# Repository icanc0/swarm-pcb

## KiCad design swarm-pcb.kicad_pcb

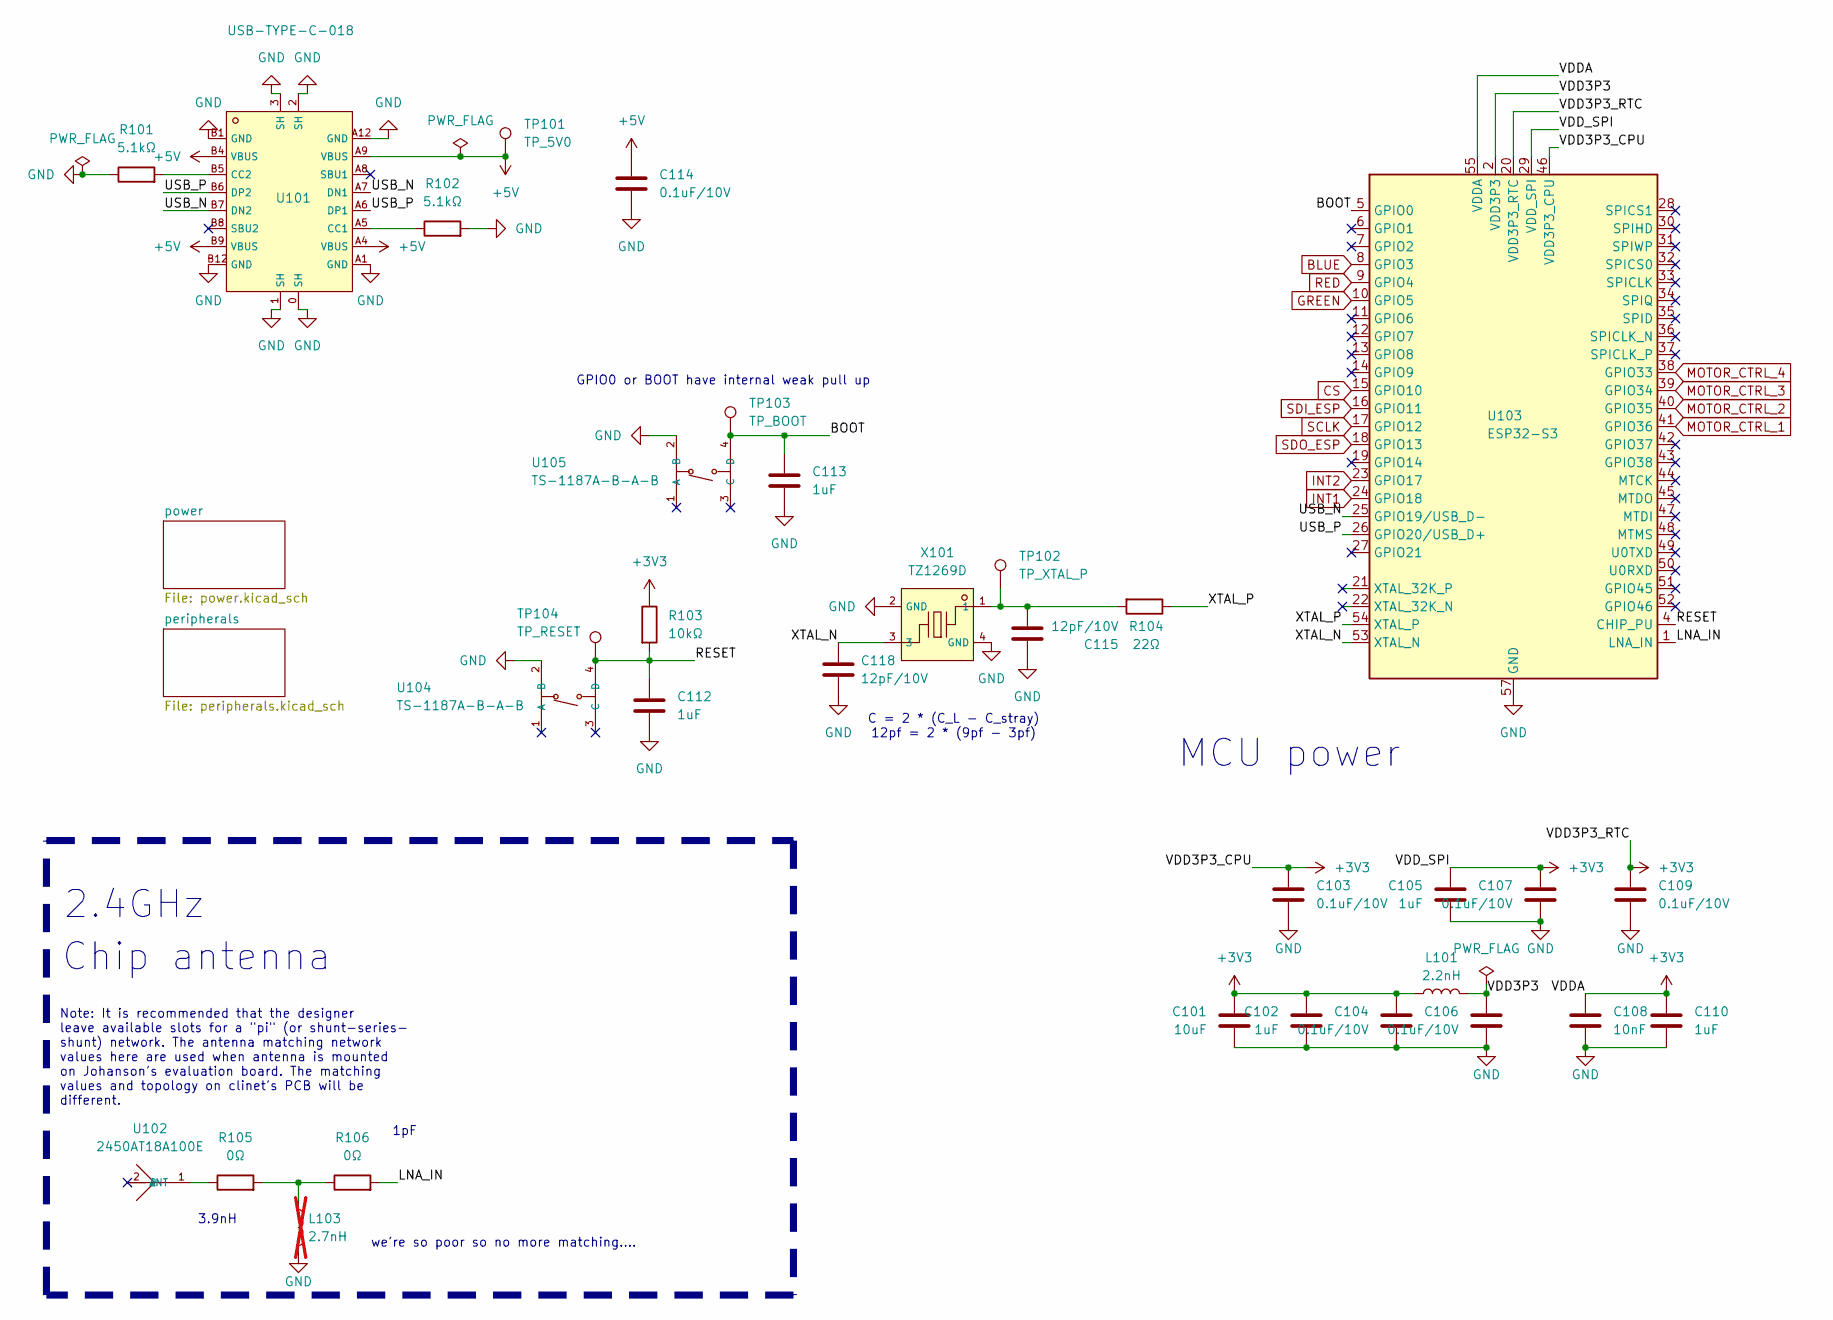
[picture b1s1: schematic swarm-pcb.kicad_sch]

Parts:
C101: 10uF; C_0603_1608Metric
C102, C105, C110, C112, C113: 1uF; C_0603_1608Metric
C103, C104, C106, C107, C109, C114: 0.1uF/10V; C_0402_1005Metric
C108: 10nF; C_0402_1005Metric
C115, C118: 12pF/10V; C_0603_1608Metric
L101: 2.2nH; L_0402_1005Metric
L103: 2.7nH; L_0402_1005Metric; not fitted
R101, R102: 5.1kΩ; R_0402_1005Metric
R103: 10kΩ; L_0402_1005Metric
R104: 22Ω; R_0402_1005Metric
R105, R106: 0Ω; R_0402_1005Metric
TP101: TP_5V0; Pin_D1.0mm_L10.0mm
TP102: TP_XTAL_P; Pin_D1.0mm_L10.0mm
TP103: TP_BOOT; Pin_D1.0mm_L10.0mm
TP104: TP_RESET; Pin_D1.0mm_L10.0mm
U101: USB-TYPE-C-018; USB-C_SMD-TYPE-C-31-M-12; LCSC C2927038
U102: 2450AT18A100E; ANT-SMD_L3.2-W1.6; LCSC C89334
U103: ESP32-S3; QFN-56-1EP_7x7mm_P0.4mm_EP4x4mm
U104, U105: TS-1187A-B-A-B; SW-SMD_4P-L5.1-W5.1-P3.70-LS6.5-TL-2; LCSC C318884
X101: TZ1269D; CRYSTAL-SMD_4P-L2.0-W1.6-BL-A; LCSC C501798

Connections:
+3V3: C101.1, C102.1, C103.1, C104.1, C105.1, C107.1, C108.1, C109.1, C110.1, L101.2, R103.1, U103.20 (VDD3P3_RTC), U103.29 (VDD_SPI), U103.46 (VDD3P3_CPU), U103.55 (VDDA), U103.56 (VDDA); also elsewhere on the board
+5V: C114.1, TP101.1, U101.A4 (VBUS), U101.A9 (VBUS), U101.B4 (VBUS), U101.B9 (VBUS); also elsewhere on the board
/BOOT: C113.1, TP103.1, U103.5 (GPIO0), U105.4 (D)
/LNA_IN: R106.2, U103.1 (LNA_IN)
/RESET: C112.1, R103.2, TP104.1, U103.4 (CHIP_PU), U104.4 (D)
/USB_N: U101.A7 (DN1), U101.B7 (DN2), U103.25 (GPIO19/USB_D-)
/USB_P: U101.A6 (DP1), U101.B6 (DP2), U103.26 (GPIO20/USB_D+)
/VDD3P3: C106.1, L101.1, U103.2 (VDD3P3), U103.3 (VDD3P3)
/XTAL_N: C118.2, U103.53 (XTAL_N), X101.3
/XTAL_P: R104.1, U103.54 (XTAL_P)
BLUE: U103.8 (GPIO3); also elsewhere on the board
CS: U103.15 (GPIO10); also elsewhere on the board
GND: C101.2, C102.2, C103.2, C104.2, C105.2, C106.2, C107.2, C108.2, C109.2, C110.2, C112.2, C113.2, C114.2, C115.2, C118.1, L103.2, R101.1, R102.2, U101.0 (SH), U101.1 (SH), U101.2 (SH), U101.3 (SH), U101.A1 (GND), U101.A12 (GND), U101.B1 (GND), U101.B12 (GND), U103.57 (GND), U104.2 (B), U105.2 (B), X101.2 (GND), X101.4 (GND); also elsewhere on the board
GREEN: U103.10 (GPIO5); also elsewhere on the board
INT1: U103.24 (GPIO18); also elsewhere on the board
INT2: U103.23 (GPIO17); also elsewhere on the board
MOTOR_CTRL_1: U103.41 (GPIO36); also elsewhere on the board
MOTOR_CTRL_2: U103.40 (GPIO35); also elsewhere on the board
MOTOR_CTRL_3: U103.39 (GPIO34); also elsewhere on the board
MOTOR_CTRL_4: U103.38 (GPIO33); also elsewhere on the board
unnamed: C115.1, R104.2, TP102.1, X101.1
unnamed: L103.1, R105.2, R106.1
unnamed: R102.1, U101.A5 (CC1)
unnamed: R101.2, U101.B5 (CC2)
unnamed: R105.1, U102.1 (ANT)
RED: U103.9 (GPIO4); also elsewhere on the board
SCLK: U103.17 (GPIO12); also elsewhere on the board
SDI_ESP: U103.16 (GPIO11); also elsewhere on the board
SDO_ESP: U103.18 (GPIO13); also elsewhere on the board

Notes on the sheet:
MCU power
2.4GHz
3.9nH
Note: It is recommended that the designer leave available slots for a "pi" (or shunt-series- shunt) network. The antenna matching network values here are used when antenna is mounted on Johanson's evaluation board. The matching values and topology on clinet's PCB will be different.
GPIO0 or BOOT have internal weak pull up
1pF
Chip antenna
we're so poor so no more matching....
C = 2 * (C_L - C_stray) 12pf = 2 * (9pf - 3pf)

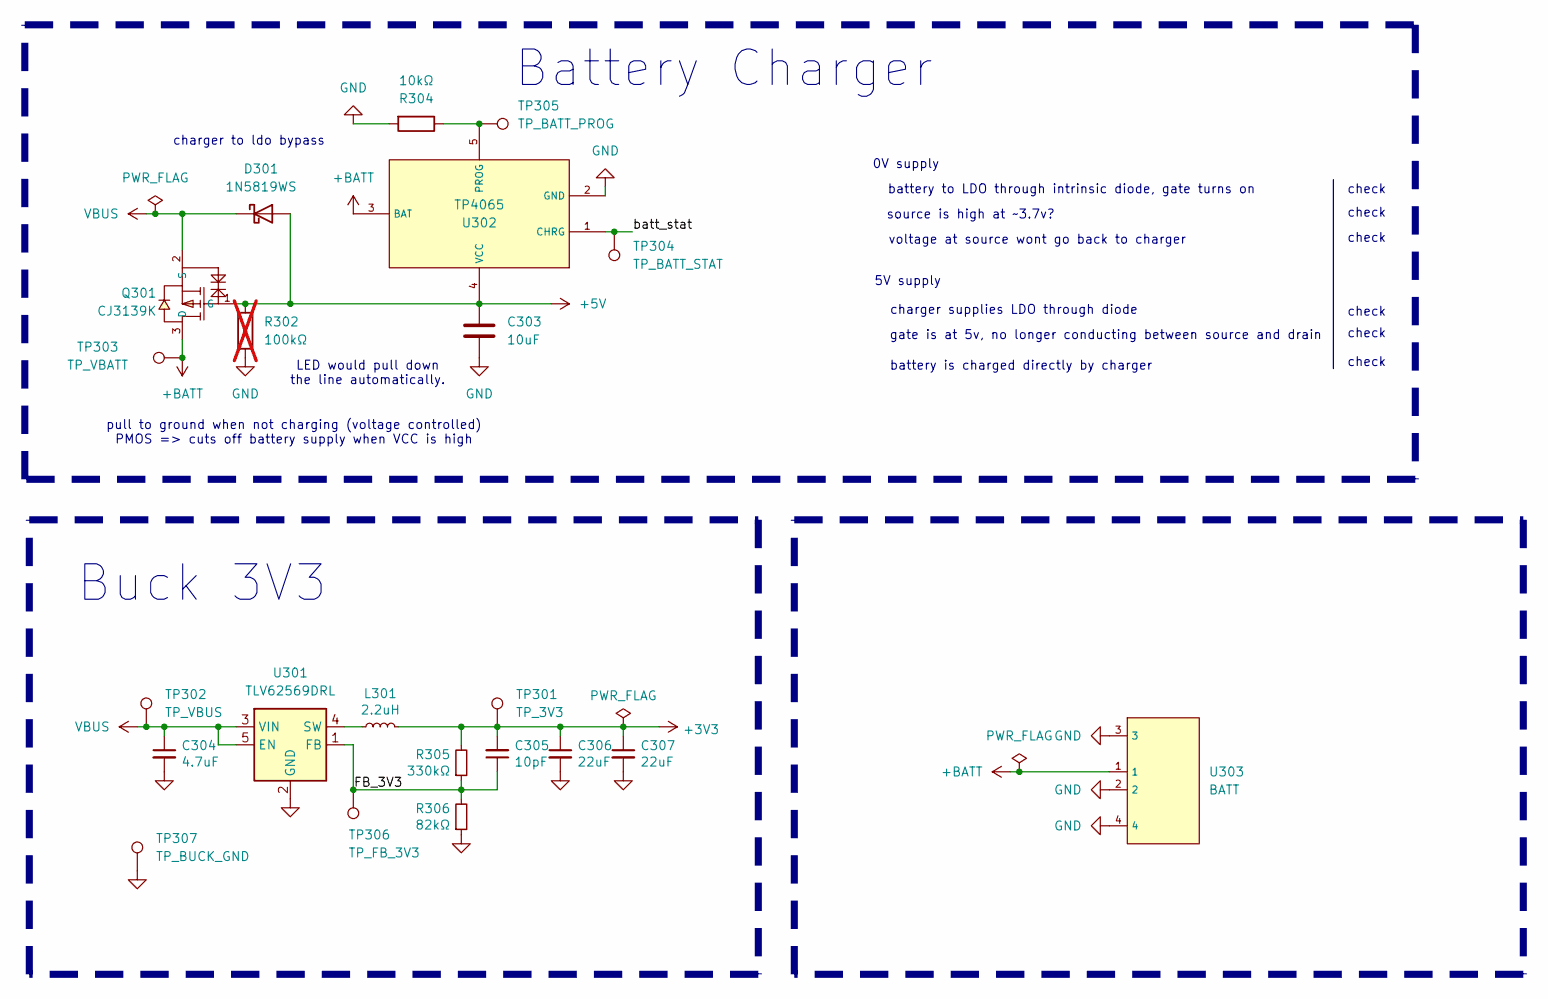
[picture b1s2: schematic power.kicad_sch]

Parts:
C303: 10uF; C_0603_1608Metric
C304: 4.7uF; C_0603_1608Metric
C305: 10pF; C_0402_1005Metric
C306, C307: 22uF; C_0603_1608Metric
D301: 1N5819WS; D_SOD-323
L301: 2.2uH; IND-SMD_L2.5-W2.0_WPN252012H
Q301: CJ3139K; SOT-723_L1.2-W0.8-P0.40-LS1.2-BR; LCSC C70022
R302: 100kΩ; L_0402_1005Metric; not fitted
R304: 10kΩ; L_0402_1005Metric
R305: 330kΩ; R_0603_1608Metric
R306: 82kΩ; R_0603_1608Metric
TP301: TP_3V3; Pin_D1.0mm_L10.0mm
TP302: TP_VBUS; Pin_D1.0mm_L10.0mm
TP303: TP_VBATT; Pin_D1.0mm_L10.0mm
TP304: TP_BATT_STAT; Pin_D1.0mm_L10.0mm
TP305: TP_BATT_PROG; Pin_D1.0mm_L10.0mm
TP306: TP_FB_3V3; Pin_D1.0mm_L10.0mm
TP307: TP_BUCK_GND; Pin_D1.0mm_L10.0mm
U301: TLV62569DRL; SOT-563
U302: TP4065; SOT-23-5_L3.0-W1.7-P0.95-LS2.8-BR; LCSC C113540
U303: BATT; CONN-TH_BM02B-SRSS-TB-LF-SN; LCSC C160388

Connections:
+3V3: C305.2, C306.1, C307.1, L301.2, R305.2, TP301.1; also elsewhere on the board
+5V: C303.1, D301.2 (A), Q301.1 (G), R302.1, U302.4 (VCC); also elsewhere on the board
+BATT: Q301.3 (D), TP303.1, U302.3 (BAT), U303.1
/power/FB_3V3: C305.1, R305.1, R306.2, TP306.1, U301.1 (FB)
/power/batt_stat: TP304.1, U302.1 (CHRG)
GND: C303.2, C304.2, C306.2, C307.2, R302.2, R304.2, R306.1, TP307.1, U301.2 (GND), U302.2 (GND), U303.2, U303.3, U303.4; also elsewhere on the board
unnamed: L301.1, U301.4 (SW)
unnamed: R304.1, TP305.1, U302.5 (PROG)
VBUS: C304.1, D301.1 (K), Q301.2 (S), TP302.1, U301.3 (VIN), U301.5 (EN)

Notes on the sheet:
check
charger supplies LDO through diode
pull to ground when not charging (voltage controlled) PMOS => cuts off battery supply when VCC is high
0V supply
Buck 3V3
source is high at ~3.7v?
Battery Charger
gate is at 5v, no longer conducting between source and drain
LED would pull down the line automatically.
battery to LDO through intrinsic diode, gate turns on
charger to ldo bypass
battery is charged directly by charger
voltage at source wont go back to charger
5V supply

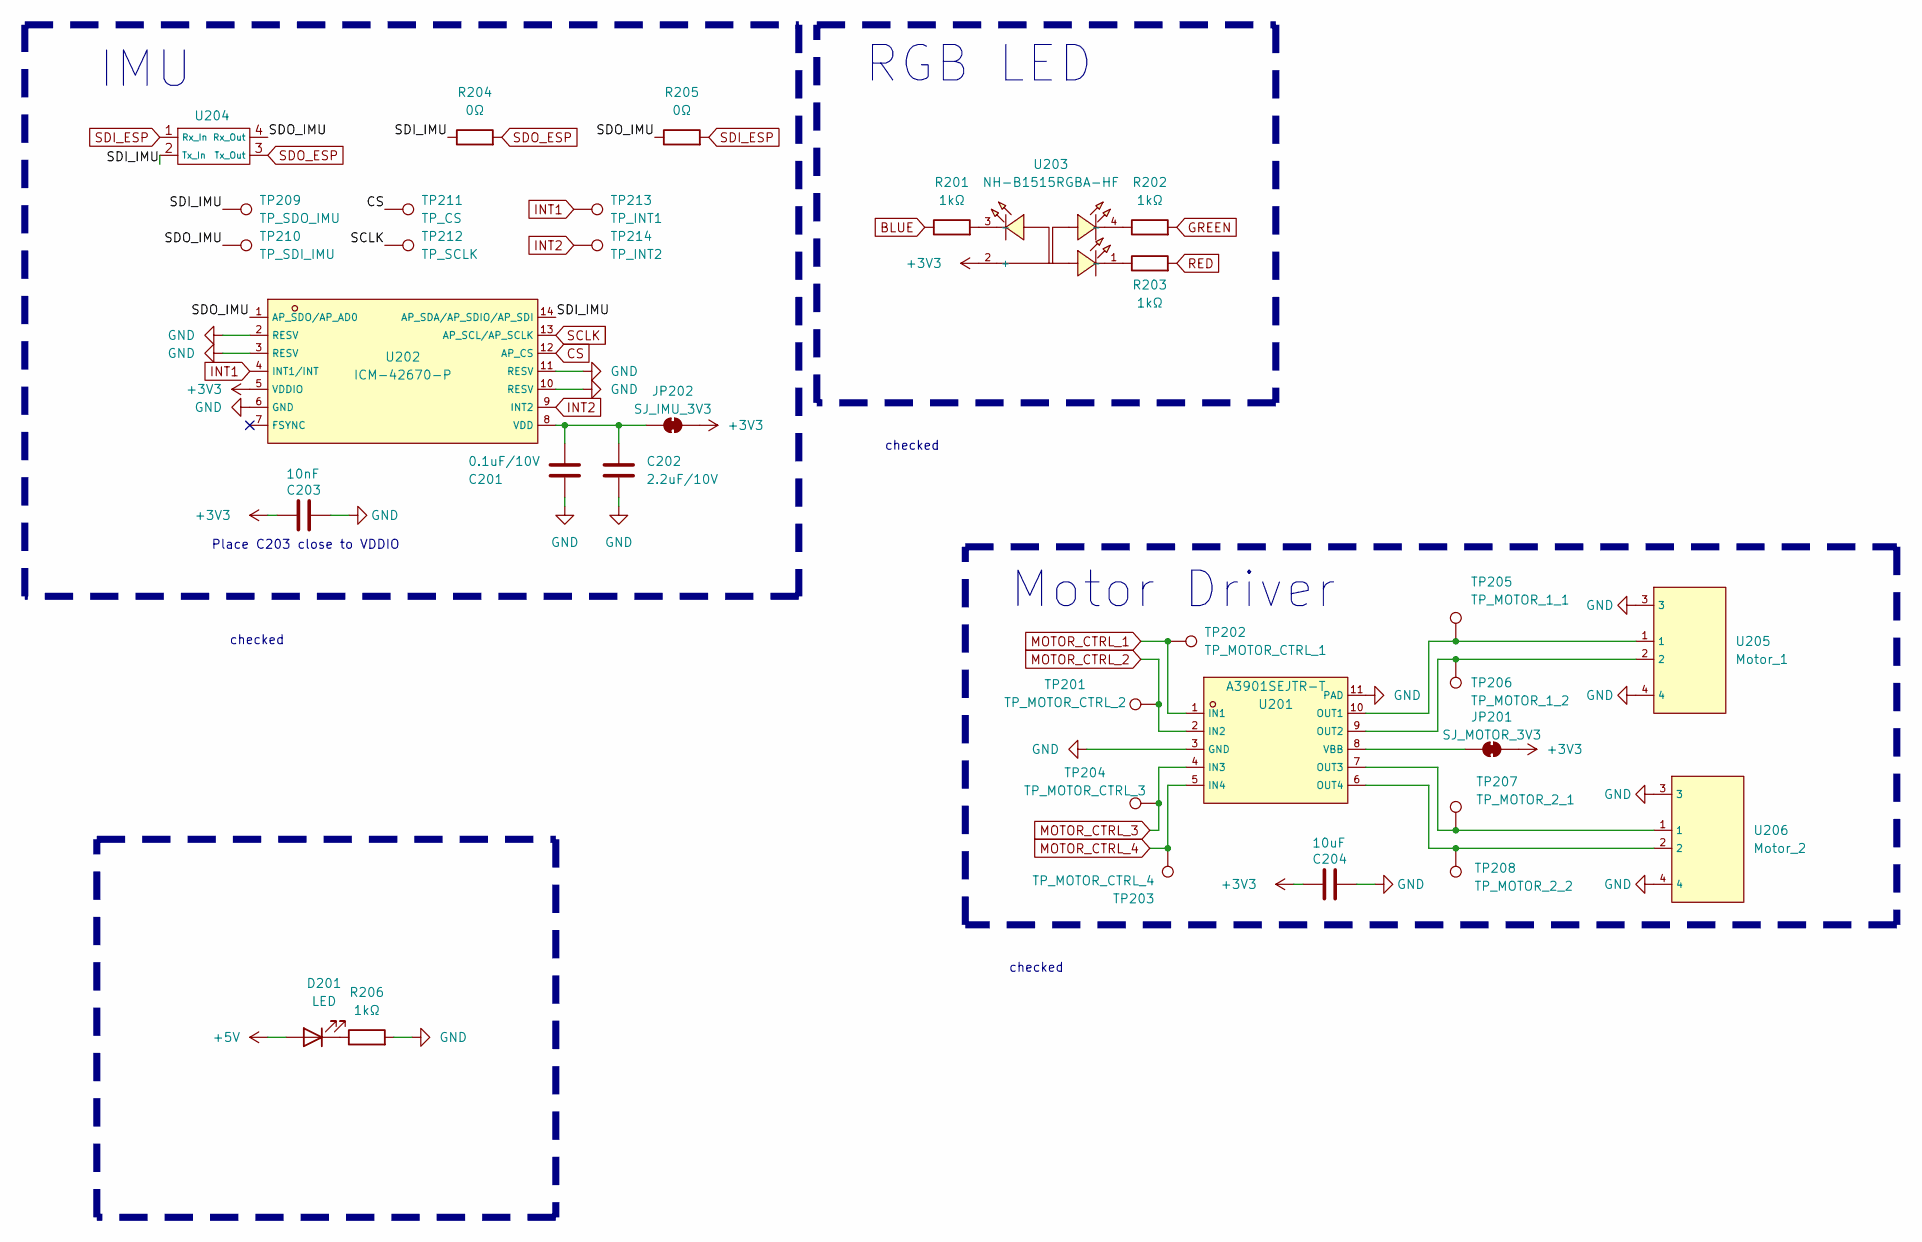
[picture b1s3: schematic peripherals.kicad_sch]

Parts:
C201: 0.1uF/10V; C_0402_1005Metric
C202: 2.2uF/10V; C_0805_2012Metric
C203: 10nF; C_0402_1005Metric
C204: 10uF; C_0603_1608Metric
D201: LED; LED_0603_1608Metric
JP201: SJ_MOTOR_3V3; SolderJumper-2_P1.3mm_Bridged_RoundedPad1.0x1.5mm
JP202: SJ_IMU_3V3; SolderJumper-2_P1.3mm_Bridged_RoundedPad1.0x1.5mm
R201, R202, R203, R206: 1kΩ; R_0402_1005Metric
R204, R205: 0Ω; R_0603_1608Metric
TP201: TP_MOTOR_CTRL_2; Pin_D1.0mm_L10.0mm
TP202: TP_MOTOR_CTRL_1; Pin_D1.0mm_L10.0mm
TP203: TP_MOTOR_CTRL_4; Pin_D1.0mm_L10.0mm
TP204: TP_MOTOR_CTRL_3; Pin_D1.0mm_L10.0mm
TP205: TP_MOTOR_1_1; Pin_D1.0mm_L10.0mm
TP206: TP_MOTOR_1_2; Pin_D1.0mm_L10.0mm
TP207: TP_MOTOR_2_1; Pin_D1.0mm_L10.0mm
TP208: TP_MOTOR_2_2; Pin_D1.0mm_L10.0mm
TP209: TP_SDO_IMU; Pin_D1.0mm_L10.0mm
TP210: TP_SDI_IMU; Pin_D1.0mm_L10.0mm
TP211: TP_CS; Pin_D1.0mm_L10.0mm
TP212: TP_SCLK; Pin_D1.0mm_L10.0mm
TP213: TP_INT1; Pin_D1.0mm_L10.0mm
TP214: TP_INT2; Pin_D1.0mm_L10.0mm
U201: A3901SEJTR-T; DFN-10_L3.0-W3.0-P0.50-BL-EP; LCSC C146403
U202: ICM-42670-P; LGA-14_L3.0-W2.5-P0.50-TL_QMI8658A; LCSC C3288646
U203: NH-B1515RGBA-HF; LED-ARRAY-SMD_4P-L1.6-W1.5-TL_NH-B1515RGBA; LCSC C2874115
U204: poka-yoke_rxtx
U205: Motor_1; CONN-TH_BM02B-SRSS-TB-LF-SN; LCSC C160388
U206: Motor_2; CONN-TH_BM02B-SRSS-TB-LF-SN; LCSC C160388

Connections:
+3V3: C203.1, C204.1, JP201.2 (B), JP202.2 (B), U202.5 (VDDIO), U203.2 (+); also elsewhere on the board
+5V: D201.2 (A); also elsewhere on the board
/peripherals/SDI_IMU: R204.1, TP209.1, U202.14 (AP_SDA/AP_SDIO/AP_SDI), U204.2 (Tx_In)
/peripherals/SDO_IMU: R205.1, TP210.1, U202.1 (AP_SDO/AP_AD0), U204.4 (Rx_Out)
BLUE: R201.1; also elsewhere on the board
CS: TP211.1, U202.12 (AP_CS); also elsewhere on the board
GND: C201.2, C202.2, C203.2, C204.2, R206.2, U201.3 (GND), U201.11 (PAD), U202.2 (RESV), U202.3 (RESV), U202.6 (GND), U202.10 (RESV), U202.11 (RESV), U205.3, U205.4, U206.3, U206.4; also elsewhere on the board
GREEN: R202.2; also elsewhere on the board
INT1: TP213.1, U202.4 (INT1/INT); also elsewhere on the board
INT2: TP214.1, U202.9 (INT2); also elsewhere on the board
MOTOR_CTRL_1: TP202.1, U201.1 (IN1); also elsewhere on the board
MOTOR_CTRL_2: TP201.1, U201.2 (IN2); also elsewhere on the board
MOTOR_CTRL_3: TP204.1, U201.4 (IN3); also elsewhere on the board
MOTOR_CTRL_4: TP203.1, U201.5 (IN4); also elsewhere on the board
unnamed: D201.1 (K), R206.1
unnamed: JP201.1 (A), U201.8 (VBB)
unnamed: C201.1, C202.1, JP202.1 (A), U202.8 (VDD)
unnamed: R201.2, U203.3 (-)
unnamed: R202.1, U203.4 (-)
unnamed: R203.1, U203.1 (-)
unnamed: TP205.1, U201.10 (OUT1), U205.1
unnamed: TP206.1, U201.9 (OUT2), U205.2
unnamed: TP207.1, U201.7 (OUT3), U206.1
unnamed: TP208.1, U201.6 (OUT4), U206.2
RED: R203.2; also elsewhere on the board
SCLK: TP212.1, U202.13 (AP_SCL/AP_SCLK); also elsewhere on the board
SDI_ESP: R205.2, U204.1 (Rx_In); also elsewhere on the board
SDO_ESP: R204.2, U204.3 (Tx_Out); also elsewhere on the board

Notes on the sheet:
checked
Motor Driver
IMU
Place C203 close to VDDIO
RGB LED

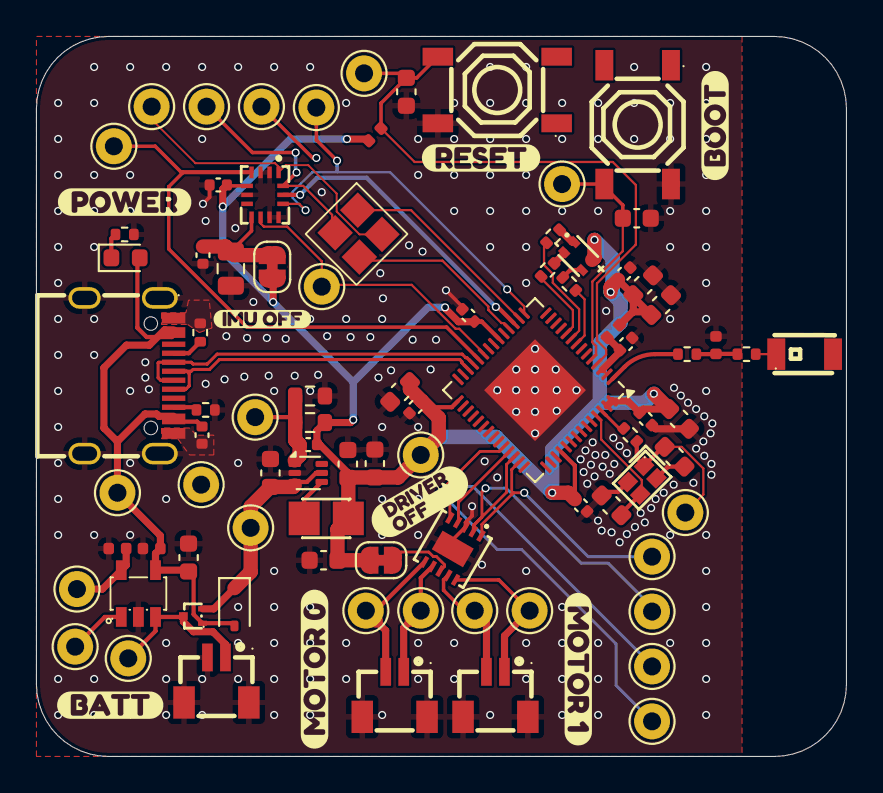
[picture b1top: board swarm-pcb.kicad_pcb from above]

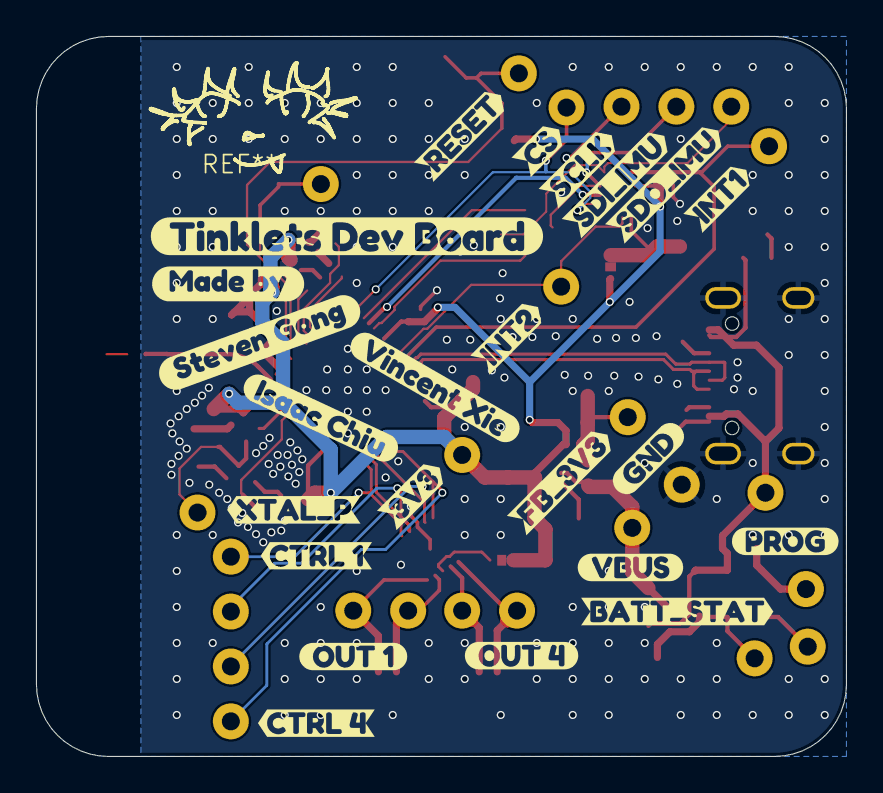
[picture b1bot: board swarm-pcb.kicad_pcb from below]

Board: 4 copper layers, 45.0 x 40.0 mm, 119 parts (23 on the bottom side), 47 nets.

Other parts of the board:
kibuzzard-672F6F41: G***; kibuzzard-672F6F41
kibuzzard-672F6FA2: G***; kibuzzard-672F6FA2
kibuzzard-672F6FAB: G***; kibuzzard-672F6FAB
kibuzzard-672F6FBA: G***; kibuzzard-672F6FBA
kibuzzard-672F6FFE: G***; kibuzzard-672F6FFE
kibuzzard-672F708E: G***; kibuzzard-672F708E
kibuzzard-672F7049: G***; kibuzzard-672F7049
kibuzzard-672F7060: G***; kibuzzard-672F7060
kibuzzard-673054F1: G***; kibuzzard-673054F1
kibuzzard-673055BA: G***; kibuzzard-673055BA
kibuzzard-673055CB: G***; kibuzzard-673055CB
kibuzzard-673055DA: G***; kibuzzard-673055DA
kibuzzard-673055F3: G***; kibuzzard-673055F3
kibuzzard-673055FE: G***; kibuzzard-673055FE
kibuzzard-673056FB: G***; kibuzzard-673056FB
kibuzzard-6730551F: G***; kibuzzard-6730551F
kibuzzard-6730552C: G***; kibuzzard-6730552C
kibuzzard-6730556D: G***; kibuzzard-6730556D
kibuzzard-6730559C: G***; kibuzzard-6730559C
kibuzzard-6730560C: G***; kibuzzard-6730560C
kibuzzard-6730561B: G***; kibuzzard-6730561B
kibuzzard-6730566E: G***; kibuzzard-6730566E
kibuzzard-6730568D: G***; kibuzzard-6730568D
kibuzzard-67305501: G***; kibuzzard-67305501
kibuzzard-67305511: G***; kibuzzard-67305511
kibuzzard-67305534: G***; kibuzzard-67305534
kibuzzard-67305547: G***; kibuzzard-67305547
kibuzzard-67305558: G***; kibuzzard-67305558
kibuzzard-67305590: G***; kibuzzard-67305590
kibuzzard-67305712: G***; kibuzzard-67305712
kibuzzard-67305722: G***; kibuzzard-67305722

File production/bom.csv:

Designator,Footprint,Quantity,Value,LCSC Part #
"C101, C204, C303",0603,3,10uF,
"C102, C105, C110, C112, C113",0603,5,1uF,
"C103, C104, C106, C107, C109, C114, C201",0402,7,0.1uF/10V,
"C108, C203",0402,2,10nF,
"C115, C118",0603,2,12pF/10V,
C202,0805,1,2.2uF/10V,
C304,0603,1,4.7uF,
C305,0402,1,10pF,
"C306, C307",0603,2,22uF,
D201,0603,1,LED,
D301,D_SOD-323,1,1N5819WS,
L101,0402,1,2.2nH,
L301,IND-SMD_L2.5-W2.0_WPN252012H,1,2.2uH,
Q301,SOT-723_L1.2-W0.8-P0.40-LS1.2-BR,1,CJ3139K,C70022
"R101, R102",0402,2,5.1kΩ,
"R103, R304",0402,2,10kΩ,
R104,0402,1,22Ω,
"R105, R106",0402,2,0Ω,
"R201, R202, R203, R206",0402,4,1kΩ,
"R204, R205",0603,2,0Ω,
R305,0603,1,330kΩ,
R306,0603,1,82kΩ,
TP101,Pin_D1.0mm_L10.0mm,1,TP_5V0,
TP102,Pin_D1.0mm_L10.0mm,1,TP_XTAL_P,
TP103,Pin_D1.0mm_L10.0mm,1,TP_BOOT,
TP104,Pin_D1.0mm_L10.0mm,1,TP_RESET,
TP201,Pin_D1.0mm_L10.0mm,1,TP_MOTOR_CTRL_2,
TP202,Pin_D1.0mm_L10.0mm,1,TP_MOTOR_CTRL_1,
TP203,Pin_D1.0mm_L10.0mm,1,TP_MOTOR_CTRL_4,
TP204,Pin_D1.0mm_L10.0mm,1,TP_MOTOR_CTRL_3,
TP205,Pin_D1.0mm_L10.0mm,1,TP_MOTOR_1_1,
TP206,Pin_D1.0mm_L10.0mm,1,TP_MOTOR_1_2,
TP207,Pin_D1.0mm_L10.0mm,1,TP_MOTOR_2_1,
TP208,Pin_D1.0mm_L10.0mm,1,TP_MOTOR_2_2,
TP209,Pin_D1.0mm_L10.0mm,1,TP_SDO_IMU,
TP210,Pin_D1.0mm_L10.0mm,1,TP_SDI_IMU,
TP211,Pin_D1.0mm_L10.0mm,1,TP_CS,
TP212,Pin_D1.0mm_L10.0mm,1,TP_SCLK,
TP213,Pin_D1.0mm_L10.0mm,1,TP_INT1,
TP214,Pin_D1.0mm_L10.0mm,1,TP_INT2,
TP301,Pin_D1.0mm_L10.0mm,1,TP_3V3,
TP302,Pin_D1.0mm_L10.0mm,1,TP_VBUS,
TP303,Pin_D1.0mm_L10.0mm,1,TP_VBATT,
TP304,Pin_D1.0mm_L10.0mm,1,TP_BATT_STAT,
TP305,Pin_D1.0mm_L10.0mm,1,TP_BATT_PROG,
TP306,Pin_D1.0mm_L10.0mm,1,TP_FB_3V3,
TP307,Pin_D1.0mm_L10.0mm,1,TP_BUCK_GND,
U101,USB-C_SMD-TYPE-C-31-M-12,1,USB-TYPE-C-018,C2927038
U102,ANT-SMD_L3.2-W1.6,1,2450AT18A100E,C89334
U103,QFN-56-1EP_7x7mm_P0.4mm_EP4x4mm,1,ESP32-S3,
"U104, U105",SW-SMD_4P-L5.1-W5.1-P3.70-LS6.5-TL-2,2,TS-1187A-B-A-B,C318884
U201,DFN-10_L3.0-W3.0-P0.50-BL-EP,1,A3901SEJTR-T,C146403
U202,LGA-14_L3.0-W2.5-P0.50-TL_QMI8658A,1,ICM-42670-P,C3288646
U203,LED-ARRAY-SMD_4P-L1.6-W1.5-TL_NH-B1515RGBA,1,NH-B1515RGBA-HF,C2874115
U204,poka-yoke_rxtx,1,~,
U205,CONN-TH_BM02B-SRSS-TB-LF-SN,1,Motor_1,C160388
U206,CONN-TH_BM02B-SRSS-TB-LF-SN,1,Motor_2,C160388
U301,SOT-563,1,TLV62569DRL,
U302,SOT-23-5_L3.0-W1.7-P0.95-LS2.8-BR,1,TP4065,C113540
U303,CONN-TH_BM02B-SRSS-TB-LF-SN,1,BATT,C160388
X101,CRYSTAL-SMD_4P-L2.0-W1.6-BL-A,1,TZ1269D,C501798

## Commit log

2024-11-09 added test points
2024-11-10 production time
2024-11-10 production
